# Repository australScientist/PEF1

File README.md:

# The Ecophysiometer: An Open-Source Multipurpose Environmental Sensor

The **Ecophysiometer** is a low-cost (\~US\$128), modular environmental monitoring platform designed to acquire rich optical data and interpret it through chemometric calibration. Developed at the Universidad Nacional de Córdoba (UNC), CONICET and the Technical University of Rheinland-Pfalz, Landau (RPTU) this project shifts analytical complexity from hardware to software, enabling multi-analyte quantification with flexible, 3D-printable instrumentation.

## 📁 Repository Structure

The project is organized to support both hardware fabrication and data analysis:

```         
/Design/Hardware: Engineering files for the flow cell, modular housing, and sensor mounts in FreeCAD and STL formats. Includes KiCAD project files for the constant-current PCB.
```

/Design/Software: Python source code including the core Measurement.py, ImageProcessor.py, and SpectralData.py layers .

/Instructions: Step-by-step assembly guides, including the critical IR filter removal tutorial for the Raspberry Pi Camera .

/Characterisation: Raw data and R scripts used to validate signal stability, linear range, and manufacturing variability.

/Implementation examples: Datasets and R models for the primary use cases: Turbidity and Phytoplankton differential quantification.

## 🛠️ Key Technical Features

```         
Software-Defined Specificity: Analyte detection is determined by chemometric calibration (PLSR, PCA) rather than fixed hardware filters.
```

High-Certainty Signal Processing: The pipeline aligns 450 vertical rows and applies 5-pixel binning, deriving each data point from the average of 2,250 measurements to maximize the signal-to-noise ratio .

Reproducible Hardware: Designed for manufacturing with minimal technical knowledge using locally available electronic materials and 3D printing in PETG .

## 🚀 Getting Started

### 1. Hardware Fabrication

```         
3D Printing: Print parts found in /Design/Hardware. Black PETG is recommended to minimize internal reflections.
```

[Circuitry]{.underline}: Fabricate the PCB using the provided KiCAD files or the CNC-ready .nc files in the Circuit Board directory.

[Sensor Modification]{.underline}: Follow Instructions/IR_REMOVAL.md to remove the IR cut-off filter from the Raspberry Pi Camera V1.3.

### 2. Software Installation

Clone this repository and install the dependencies: Bash

git clone <https://github.com/australScientist/PEF1.git> cd PEF1 pip install -r Design/Software/PEF0/requirements.txt

### 3. Basic Operation

[Calibration]{.underline}: Run test.py to identify the linear integration time for your specific hardware assembly .

[Measurement]{.underline}: Launch the graphical interface: Bash

```         
python3 Design/Software/PEF0/src/GUI2.py
```

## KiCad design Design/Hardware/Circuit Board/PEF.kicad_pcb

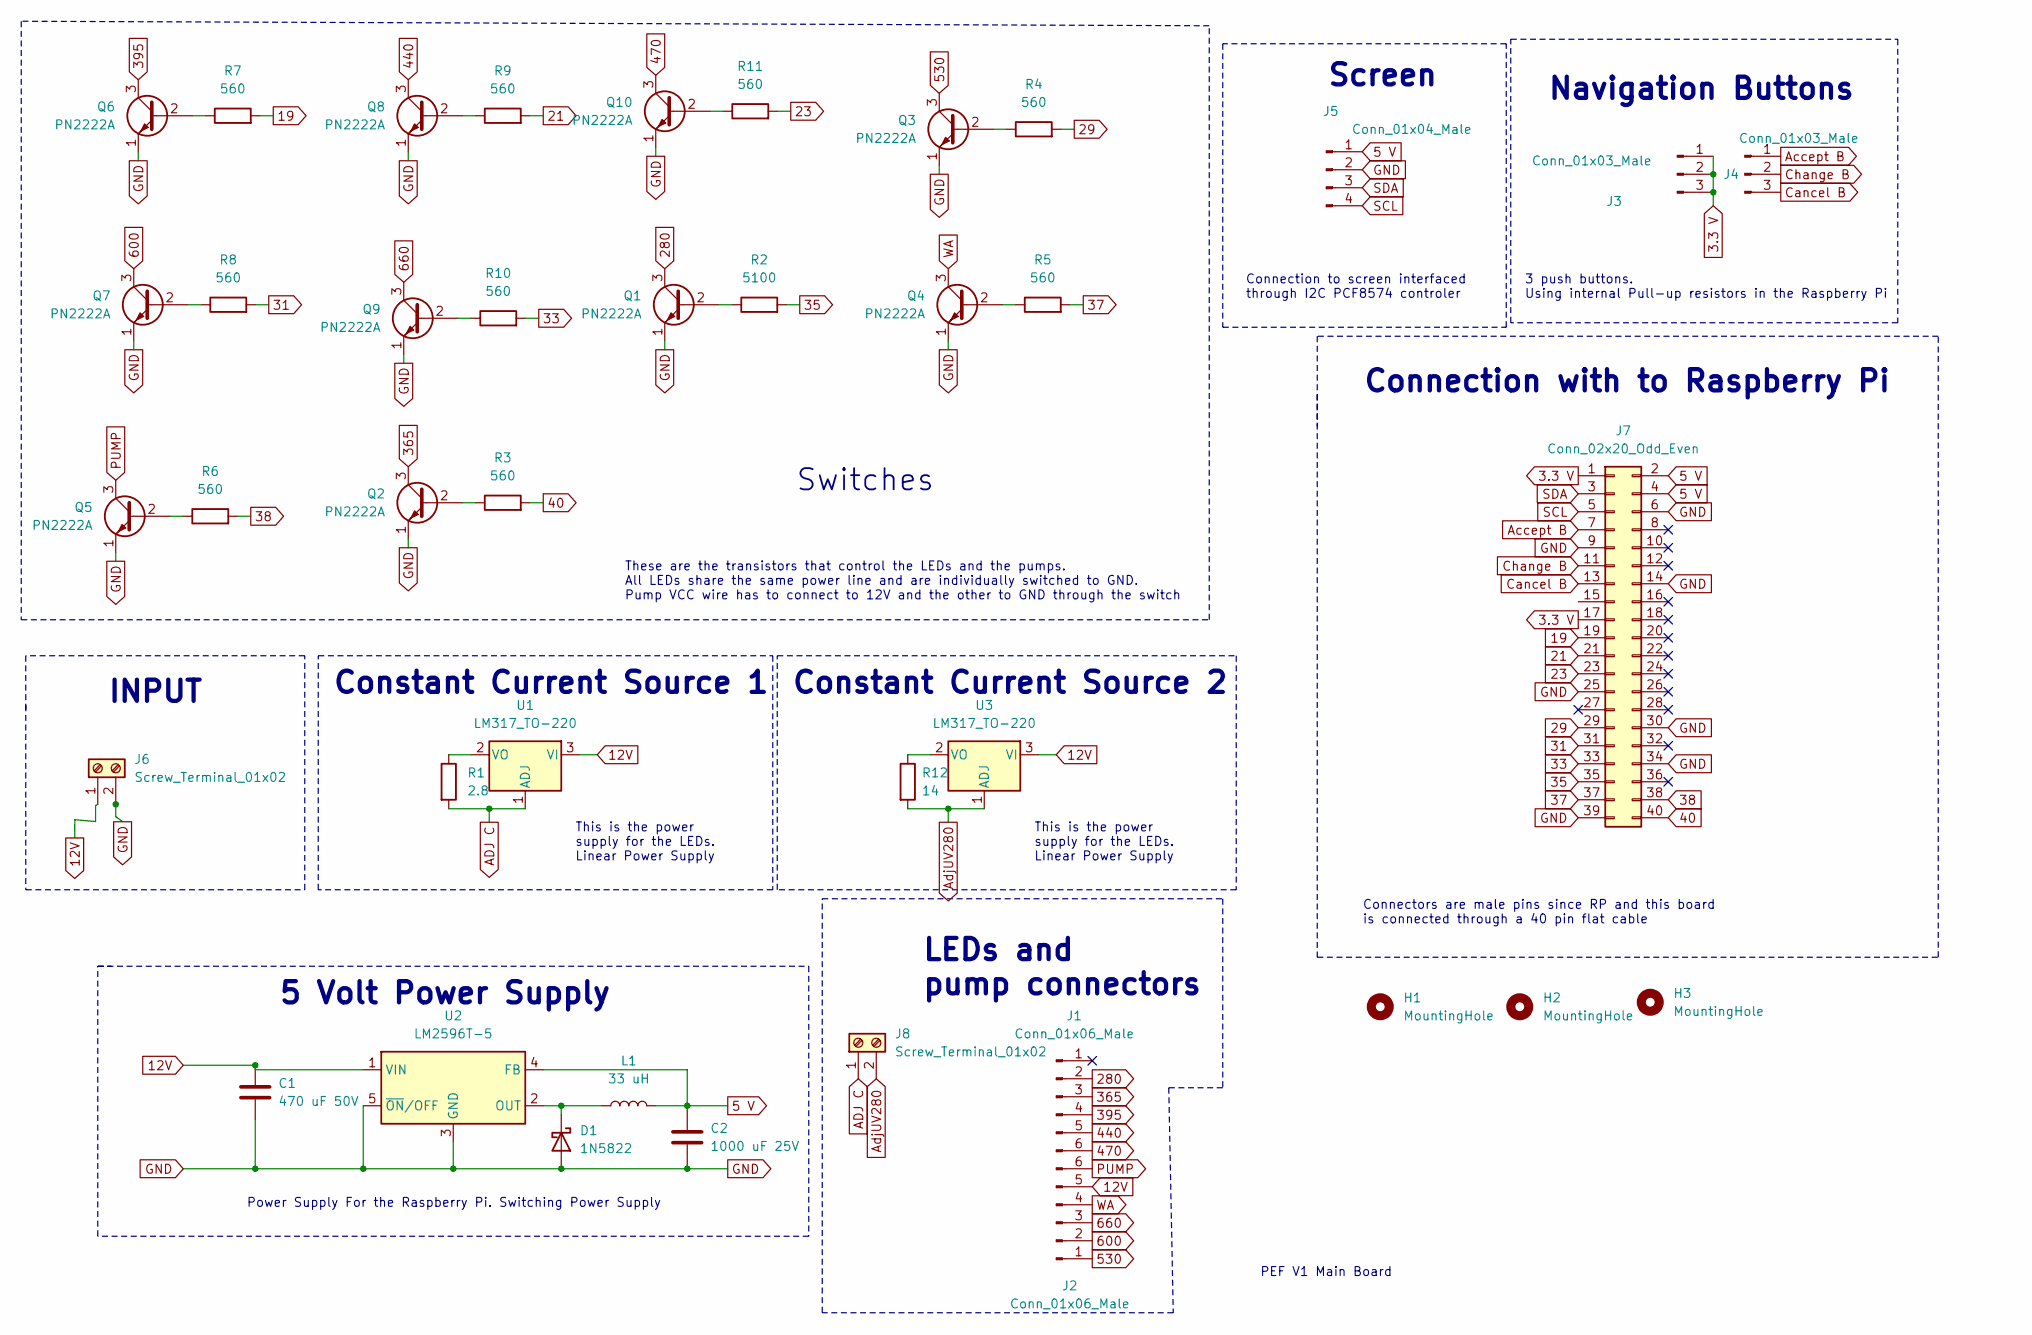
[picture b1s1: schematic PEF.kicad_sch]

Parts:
C1: 470 uF 50V; C_Radial_D10.0mm_H20.0mm_P5.00mm
C2: 1000 uF 25V; C_Radial_D8.0mm_H11.5mm_P3.50mm
D1: 1N5822; D_DO-201AD_P15.24mm_Horizontal
H1, H2, H3: MountingHole; MountingHole_5mm
J1, J2: Conn_01x06_Male; PhoenixContact_MSTBA_2,5_6-G-5,08_1x06_P5.08mm_Horizontal
J3, J4: Conn_01x03_Male; PinHeader_1x03_P2.54mm_Vertical
J5: Conn_01x04_Male; PinHeader_1x04_P2.54mm_Vertical
J6, J8: Screw_Terminal_01x02; TerminalBlock_Phoenix_MKDS-1,5-2_1x02_P5.00mm_Horizontal
J7: Conn_02x20_Odd_Even; PinHeader_2x20_P2.54mm_Vertical
L1: 33 uH; L_Radial_D7.2mm_P3.00mm_Murata_1700
Q1, Q2, Q3, Q4, Q5, Q6, Q7, Q8, Q9, Q10: PN2222A; TO-92_Inline
R1: 2.8; R_Axial_DIN0207_L6.3mm_D2.5mm_P10.16mm_Horizontal
R2: 5100; R_Axial_DIN0207_L6.3mm_D2.5mm_P10.16mm_Horizontal
R3, R4, R5, R6, R7, R8, R9, R10, R11: 560; R_Axial_DIN0207_L6.3mm_D2.5mm_P10.16mm_Horizontal
R12: 14; R_Axial_DIN0207_L6.3mm_D2.5mm_P10.16mm_Horizontal
U1, U3: LM317_TO-220; TO-220-3_Vertical
U2: LM2596T-5; TO-220-5_P3.4x3.7mm_StaggerOdd_Lead3.8mm_Vertical

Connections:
3.3 V: J3.1, J3.2, J3.3, J7.1, J7.17
5 V: C2.1, J5.1, J7.2, J7.4, L1.2, U2.4 (FB)
12V: C1.1, J2.5, J6.1, U1.3 (VI), U2.1 (VIN), U3.3 (VI)
19: J7.19, R7.2
21: J7.21, R9.2
23: J7.23, R11.2
29: J7.29, R4.2
31: J7.31, R8.2
33: J7.33, R10.2
35: J7.35, R2.2
37: J7.37, R5.2
38: J7.38, R6.2
40: J7.40, R3.2
280: J1.2, Q1.3 (C)
365: J1.3, Q2.3 (C)
395: J1.4, Q6.3 (C)
440: J1.5, Q8.3 (C)
470: J1.6, Q10.3 (C)
530: J2.1, Q3.3 (C)
600: J2.2, Q7.3 (C)
660: J2.3, Q9.3 (C)
ADJ C: J8.1, R1.2, U1.1 (ADJ)
Accept B: J4.1, J7.7
AdjUV280: J8.2, R12.2, U3.1 (ADJ)
Cancel B: J4.3, J7.13
Change B: J4.2, J7.11
GND: C1.2, C2.2, D1.2 (A), J5.2, J6.2, J7.6, J7.9, J7.14, J7.25, J7.30, J7.34, J7.39, Q1.1 (E), Q2.1 (E), Q3.1 (E), Q4.1 (E), Q5.1 (E), Q6.1 (E), Q7.1 (E), Q8.1 (E), Q9.1 (E), Q10.1 (E), U2.3 (GND), U2.5 (~ON/OFF)
unnamed: D1.1 (K), L1.1, U2.2 (OUT)
unnamed: Q1.2 (B), R2.1
unnamed: Q2.2 (B), R3.1
unnamed: Q3.2 (B), R4.1
unnamed: Q4.2 (B), R5.1
unnamed: Q5.2 (B), R6.1
unnamed: Q6.2 (B), R7.1
unnamed: Q7.2 (B), R8.1
unnamed: Q8.2 (B), R9.1
unnamed: Q9.2 (B), R10.1
unnamed: Q10.2 (B), R11.1
unnamed: R1.1, U1.2 (VO)
unnamed: R12.1, U3.2 (VO)
PUMP: J2.6, Q5.3 (C)
SCL: J5.4, J7.5
SDA: J5.3, J7.3
WA: J2.4, Q4.3 (C)

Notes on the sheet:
PEF V1 Main Board
Constant Current Source 1
LEDs and pump connectors
Connection with to Raspberry Pi
Power Supply For the Raspberry Pi. Switching Power Supply
5 Volt Power Supply
Constant Current Source 2
Screen
Connection to screen interfaced through I2C PCF8574 controler
3 push buttons. Using internal Pull-up resistors in the Raspberry Pi
INPUT
These are the transistors that control the LEDs and the pumps. All LEDs share the same power line and are individually switched to GND. Pump VCC wire has to connect to 12V and the other to GND through the switch
Connectors are male pins since RP and this board is connected through a 40 pin flat cable
Switches
Navigation Buttons
This is the power supply for the LEDs. Linear Power Supply

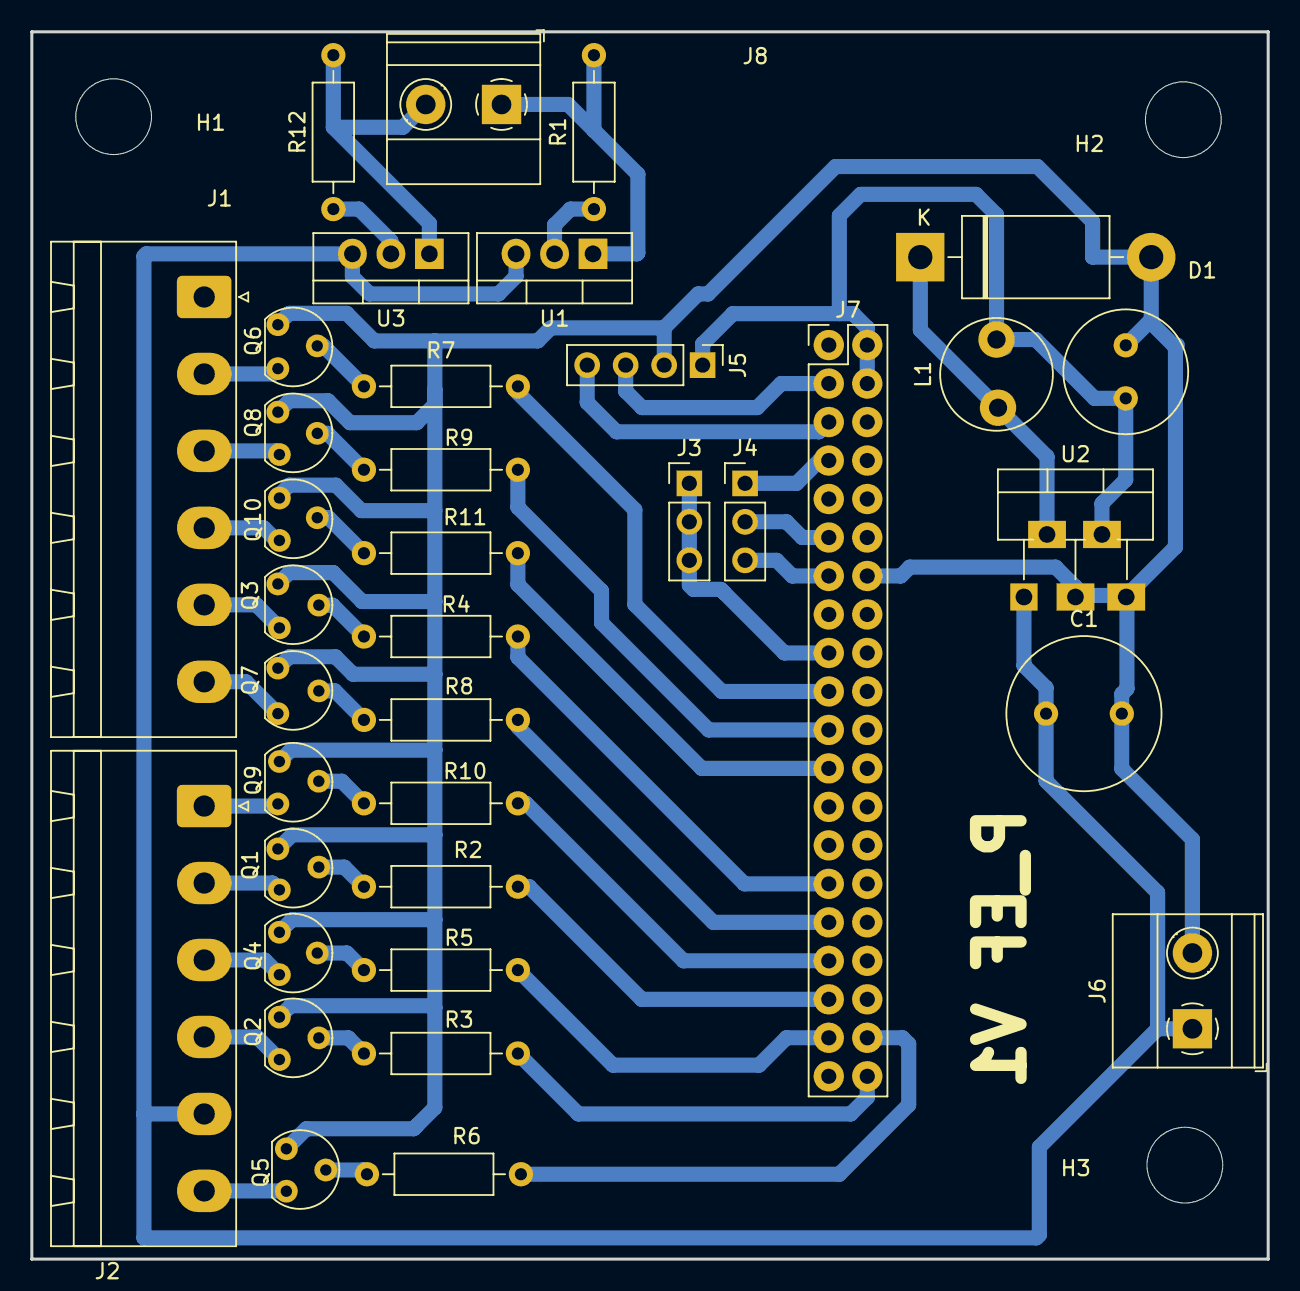
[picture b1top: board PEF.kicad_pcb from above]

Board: 2 copper layers, 81.6 x 81.0 mm, 40 parts (0 on the bottom side), 44 nets.

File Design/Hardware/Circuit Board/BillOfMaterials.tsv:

Reference	Value	Datasheet	Footprint	Qty	DNP
C1	470 uF 50V	~	Capacitor_THT:C_Radial_D10.0mm_H20.0mm_P5.00mm	1	
C2	1000 uF 25V	~	Capacitor_THT:C_Radial_D8.0mm_H11.5mm_P3.50mm	1	
D1	1N5822	http://www.vishay.com/docs/88526/1n5820.pdf	Diode_THT:D_DO-201AD_P15.24mm_Horizontal	1	
H1,H2,H3	MountingHole	~	MountingHole:MountingHole_5mm	3	
J1,J2	Conn_01x06_Male	~	Connector_Phoenix_MSTB:PhoenixContact_MSTBA_2,5_6-G-5,08_1x06_P5.08mm_Horizontal	2	
J3,J4	Conn_01x03_Male	~	Connector_PinHeader_2.54mm:PinHeader_1x03_P2.54mm_Vertical	2	
J5	Conn_01x04_Male	~	Connector_PinHeader_2.54mm:PinHeader_1x04_P2.54mm_Vertical	1	
J6,J8	Screw_Terminal_01x02	~	TerminalBlock_Phoenix:TerminalBlock_Phoenix_MKDS-1,5-2_1x02_P5.00mm_Horizontal	2	
J7	Conn_02x20_Odd_Even	~	Connector_PinHeader_2.54mm:PinHeader_2x20_P2.54mm_Vertical	1	
L1	33 uH	~	Inductor_THT:L_Radial_D7.2mm_P3.00mm_Murata_1700	1	
Q1,Q2,Q3,Q4,Q5,Q6,Q7,Q8,Q9,Q10	PN2222A	https://www.onsemi.com/pub/Collateral/PN2222-D.PDF	Package_TO_SOT_THT:TO-92_Inline	10	
R1	2.8	~	Resistor_THT:R_Axial_DIN0207_L6.3mm_D2.5mm_P10.16mm_Horizontal	1	
R2	5100	~	Resistor_THT:R_Axial_DIN0207_L6.3mm_D2.5mm_P10.16mm_Horizontal	1	
R3,R4,R5,R6,R7,R8,R9,R10,R11	560	~	Resistor_THT:R_Axial_DIN0207_L6.3mm_D2.5mm_P10.16mm_Horizontal	9	
R12	14	~	Resistor_THT:R_Axial_DIN0207_L6.3mm_D2.5mm_P10.16mm_Horizontal	1	
U1,U3	LM317_TO-220	http://www.ti.com/lit/ds/symlink/lm317.pdf	Package_TO_SOT_THT:TO-220-3_Vertical	2	
U2	LM2596T-5	http://www.ti.com/lit/ds/symlink/lm2596.pdf	Package_TO_SOT_THT:TO-220-5_P3.4x3.7mm_StaggerOdd_Lead3.8mm_Vertical	1

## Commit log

2026-01-03 Initial commit: Complete Ecophysiometer files to build an Ecophysiometer (software, hardware and configuration files). Also, two implementation cases and characterisation experiments
2026-01-05 Improving IR filter removal tutorial
2026-01-05 Readme
